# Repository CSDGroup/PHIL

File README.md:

# PHIL

Pipetting Helper Imaging Lid – PHIL - 2021

Latest Update:
15.05.2022 - Updated Arduino Mega Shield to prevent burnouts by increasing the width of motor power traces:
https://www.pcbway.com/project/shareproject/Arduino_Mega14x_V4_3edde2c7.html

Open-source personal pipetting robots with live-​cell incubation and microscopy compatibility

Overview
- personal small desktop liquid handling robot designed in AutoCAD 2018.
- small, light, cheap
- fast self-​assembly from 3D printed and commercial parts
- long-​term live cell culture media exchange, immunostainings, etc
- compatible with microscope stage-​top use during time-​lapse microscopy
- user-​friendly control software

Reference

If you use PHIL please cite the following paper:

Dettinger*, Dettinger*, Kull, Arekatla, Ahmed, Zhang, Schneiter, Wehling, Schirmacher, Kawamura, Loeffler, Schroeder*
Open-source personal pipetting robots with live-cell incubation and microscopy compatibility
Nature Communications 13, 2999 (2022).
https://doi.org/10.1038/s41467-022-30643-7

System Requirements

Hardware requirements

PHILs GUI requires only a standard computer with enough RAM to support the in-memory operations.

Software requirements

OS Requirements

This package is supported for Windows and requires Matlab 2020. The package has been tested on the following systems:

Windows 10 - Matlab 2020

This project is covered under the MIT License.

Download Files
Current version
PHIL_Complete_Resources_210716.zip (ZIP, 47.2 MB)vertical_align_bottom
2021.07.16: Added companies with international shipping options to «Order_List.xlsx» in PHIL_Complete_Resources.zip

Previous versions
2021.07.05: PHIL_Complete_Resources - .zip (ZIP, 47.2 MB)vertical_align_bottom

ZIP file contents
PHIL operation
PHIL_Operation_Instructions.pdf: Complete instructions for using PHIL
PHIL_GUI_210602.m: Executable Matlab script for PHIL gui

PHIL production
Order_List.xlsx: Complete parts list for all required parts
PHIL_Print_Instructions.pdf: Full print settings of all parts
3D print files as described below
PHIL_Assembly_Instructions.pdf: Full instructions for PHIL assembly
PHIL_Arduino_MEGA_14Pump_210216.ino: Complete Arduino sketch for PHIL operation. Requires Accelstepper library installed
 
3D print files
Individual components are encoded by the individual STL files below. You can use these to print them individually.
All required components for a PHIL robot have been grouped into 10 sets for easy simultaneous printing of several components in one print session.

Set_1.stl
Body_VB1.stl: Main body of PHIL
Body_Top_VB1.stl: Frame for mounting Z-axis stepper motors
Elbow_Left_VB1.stl: Left actuator arm for mounting limit switches
Elbow_Right_VB1.stl: Right actuator arm for mounting limit switches
Hands_VB1.stl: Left and right actuator arm
Tube_Plug_VB1.stl: Tube holder for PHIL body

Set_2.stl
Arm_Plate_VB1.stl: Stepper motor mount for left and right arms
Body_Bottom_VB1.stl: Base for main body of PHIL
 
 
Set_3_100infill.stl
LR_Arm_100Infill.stl: Left and right arms for PHIL. To be printed at 100% infill

Set_4.stl
Chamber _VB1.stl: Incubator chamber
2 x Screw_VB1.stl: Screw drives for z-axis
 
 
Set_5.stl
Chamber_Lid_VB1.stl: Lid for incubator chamber
USB_Back_VB1.stl: USB cable mounting bracket, back
USB_Front_VB1.stl: USB cable mounting bracket, front
Handle_VB1.stl: Handle for power control box
Pin_Cup_V1.stl: Pipet holder for normal wells
(Pin_Cup_V1.stl can be replaced with Pin_Cup_Deep_Well_VB1.stl when working with deep well multiwell plates - see instructions)
 
 
Set_6.stl
Power_Box_Left_VB1.stl: Left half of power control box
 
 
Set_7.stl
Power_Box_Right_VB1.stl: Right half of power control box
 
 
Set_8.stl
Arduino_Plate_VB1.stl: Plate for mounting arduinos
 
 
Set_9.stl
Mount_1x_31.stl: 6x mounting brackets for peristaltic pump
 
 
Set_10.stl
Wheel_1x_31.stl: 6x rotors for peristaltic pump

The following files are not required for a PHIL, but help the production:

tube_bender_top_v2.stl: Tube bending press outer body
tube_bender_bot_v2.stl: Tube bending press inner frame
85mm_Tube_cutter_v2.stl: Jig for cutting 85mm segment of peristaltic pump tubing

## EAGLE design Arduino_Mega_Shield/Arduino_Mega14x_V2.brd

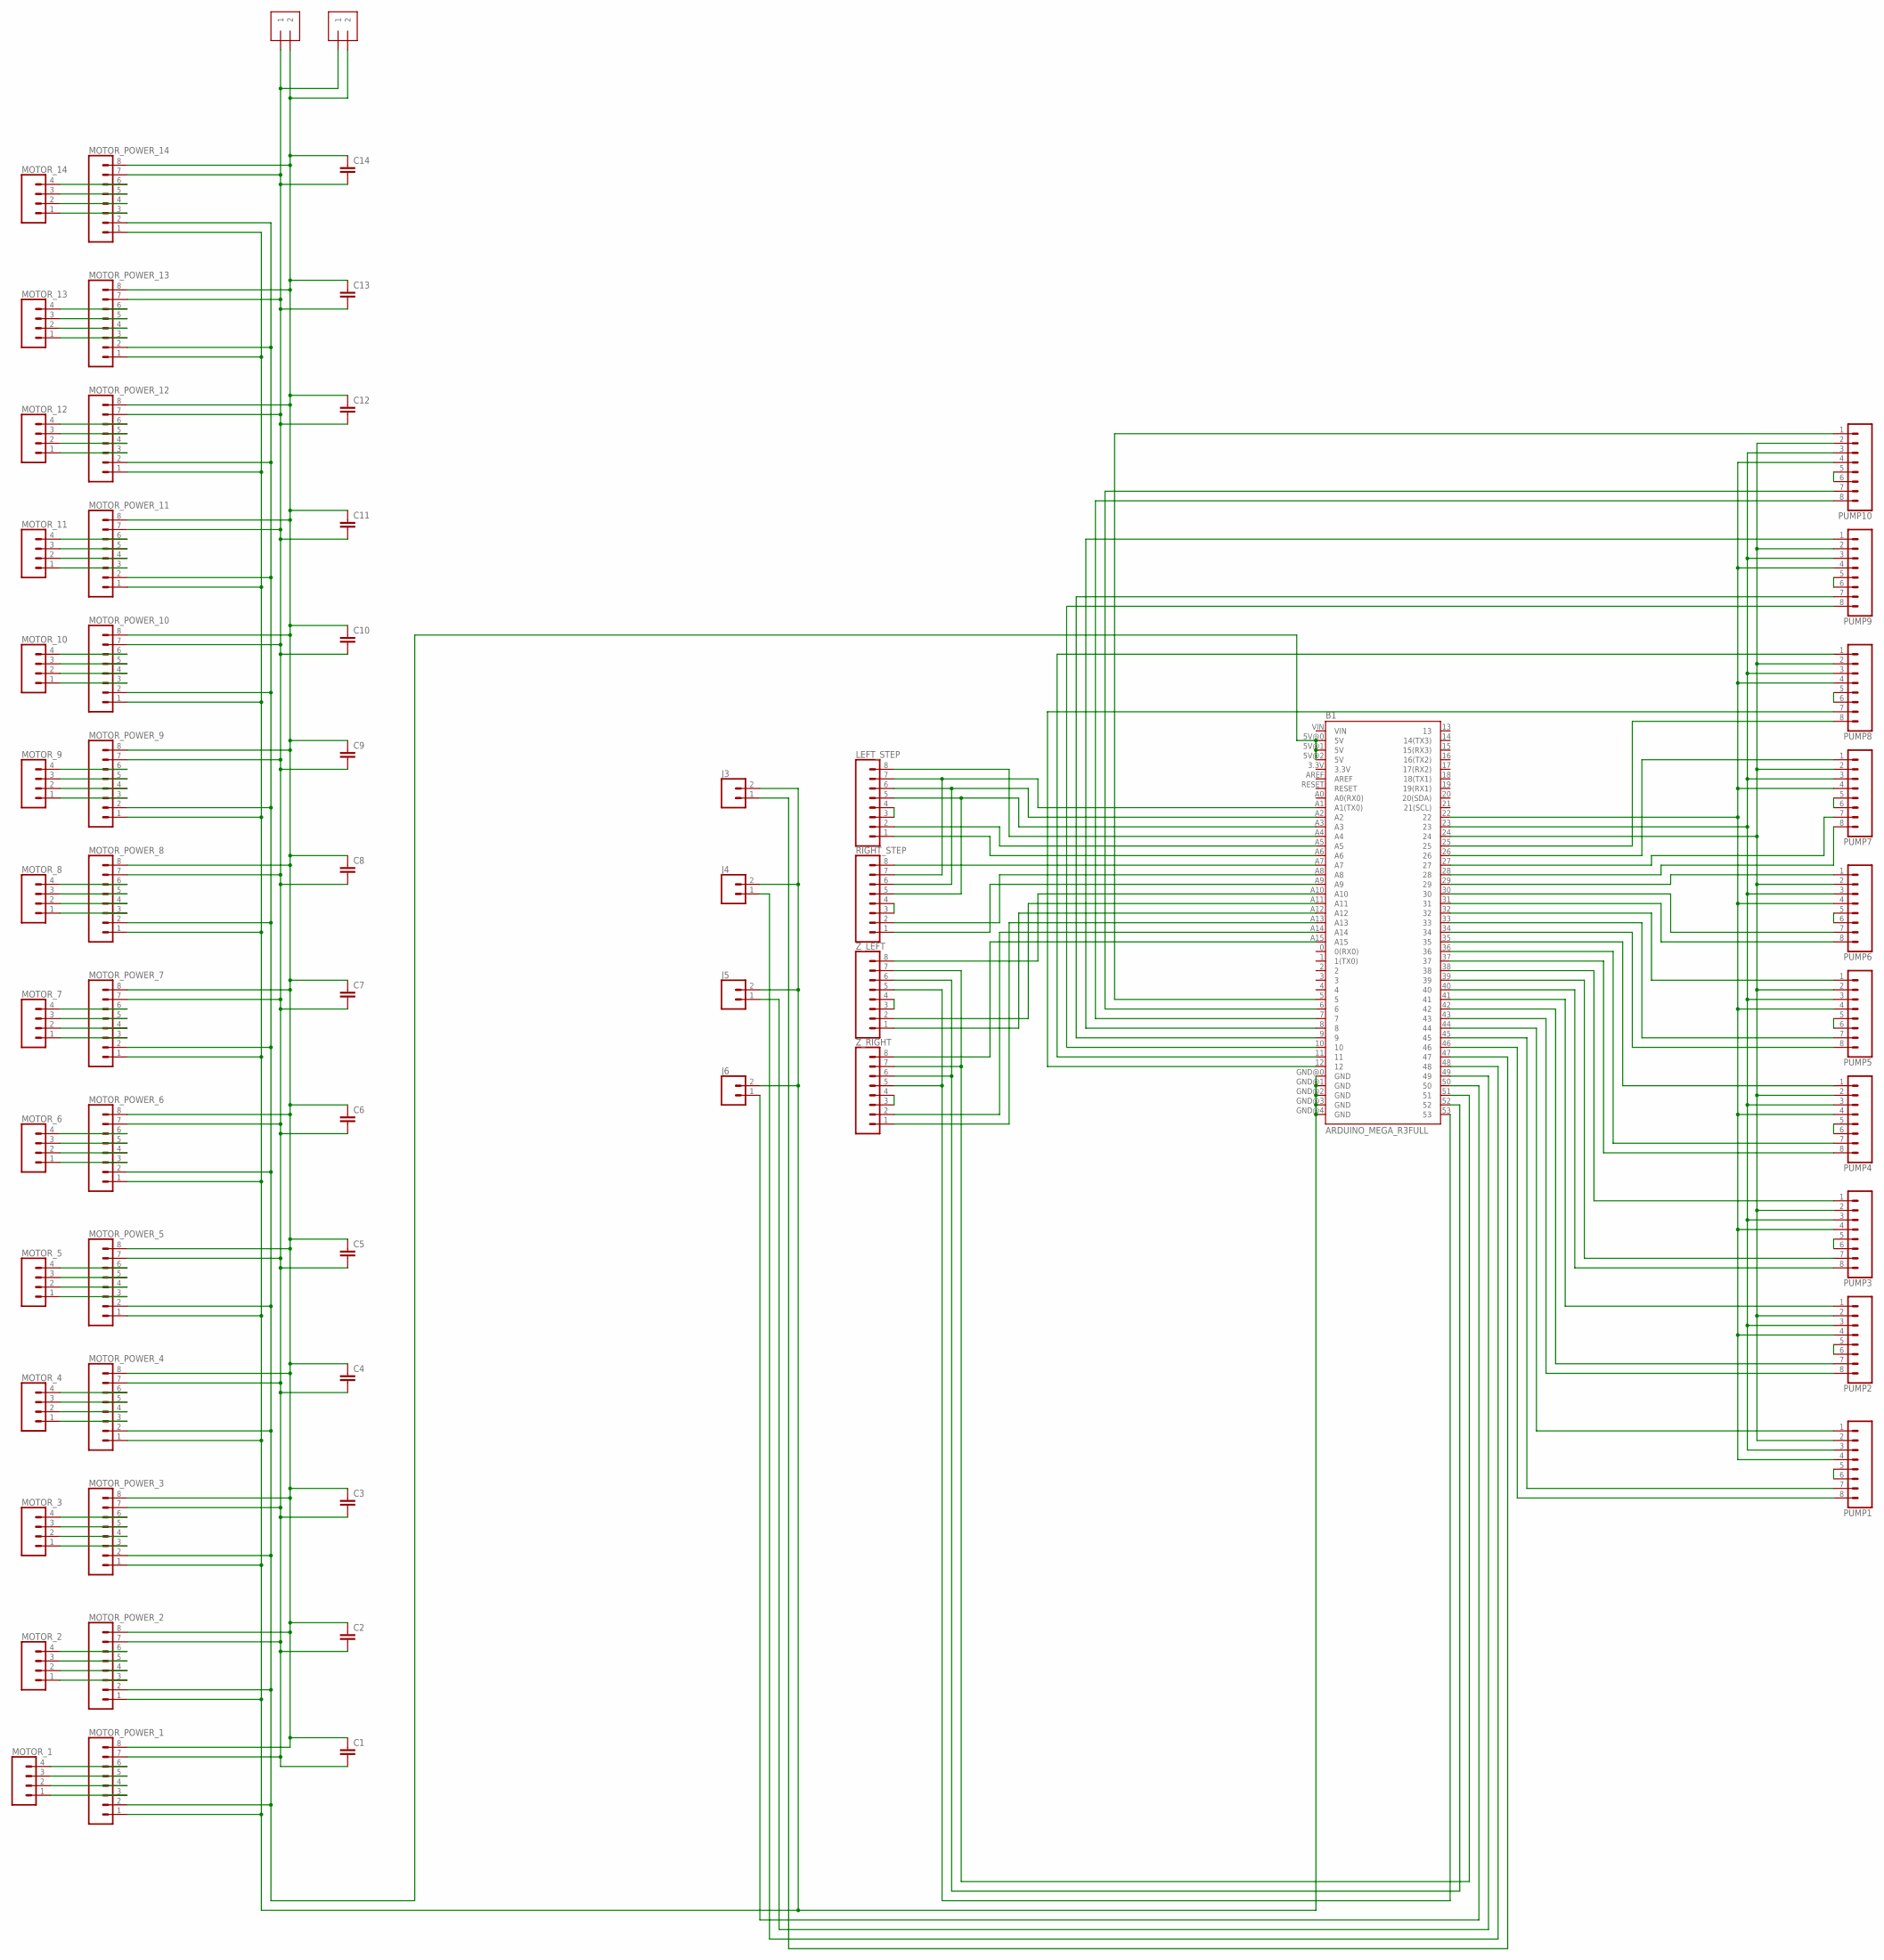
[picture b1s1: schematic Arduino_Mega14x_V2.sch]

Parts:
B1: ARDUINO_MEGA_R3FULL; ARDUINO_MEGA
C1, C2, C3, C4, C5, C6, C7, C8, C9, C10, C11, C12, C13, C14: C5/2.5; C5B2.5
J1, J2: 1X2-3.5MM
J3, J4, J5, J6: CONN_02; 1X02
LEFT_STEP: CONN_08"; 1X08
MOTOR_1, MOTOR_2, MOTOR_3, MOTOR_4, MOTOR_5, MOTOR_6, MOTOR_7, MOTOR_8, MOTOR_9, MOTOR_10, MOTOR_11, MOTOR_12, MOTOR_13, MOTOR_14: CONN_04; 1X04
MOTOR_POWER_1, MOTOR_POWER_2, MOTOR_POWER_3, MOTOR_POWER_4, MOTOR_POWER_5, MOTOR_POWER_6, MOTOR_POWER_7, MOTOR_POWER_8, MOTOR_POWER_9, MOTOR_POWER_10, MOTOR_POWER_11, MOTOR_POWER_12, MOTOR_POWER_13, MOTOR_POWER_14: CONN_08"; 1X08
PUMP1, PUMP2, PUMP3, PUMP4, PUMP5, PUMP6, PUMP7, PUMP8, PUMP9, PUMP10: CONN_08"; 1X08
RIGHT_STEP: CONN_08"; 1X08
Z_LEFT: CONN_08"; 1X08
Z_RIGHT: CONN_08"; 1X08

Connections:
unnamed: MOTOR_1.1, MOTOR_POWER_1.3
unnamed: MOTOR_1.2, MOTOR_POWER_1.4
unnamed: MOTOR_1.3, MOTOR_POWER_1.5
unnamed: LEFT_STEP.3, LEFT_STEP.4
unnamed: MOTOR_1.4, MOTOR_POWER_1.6
unnamed: MOTOR_2.1, MOTOR_POWER_2.3
unnamed: MOTOR_2.2, MOTOR_POWER_2.4
unnamed: RIGHT_STEP.3, RIGHT_STEP.4
unnamed: MOTOR_2.3, MOTOR_POWER_2.5
unnamed: MOTOR_2.4, MOTOR_POWER_2.6
unnamed: MOTOR_3.1, MOTOR_POWER_3.3
unnamed: MOTOR_3.2, MOTOR_POWER_3.4
unnamed: MOTOR_3.3, MOTOR_POWER_3.5
unnamed: MOTOR_3.4, MOTOR_POWER_3.6
unnamed: MOTOR_4.1, MOTOR_POWER_4.3
unnamed: MOTOR_4.2, MOTOR_POWER_4.4
unnamed: MOTOR_4.3, MOTOR_POWER_4.5
unnamed: Z_LEFT.3, Z_LEFT.4
unnamed: MOTOR_4.4, MOTOR_POWER_4.6
unnamed: MOTOR_5.1, MOTOR_POWER_5.3
unnamed: MOTOR_5.2, MOTOR_POWER_5.4
unnamed: MOTOR_5.3, MOTOR_POWER_5.5
unnamed: MOTOR_5.4, MOTOR_POWER_5.6
unnamed: MOTOR_6.1, MOTOR_POWER_6.3
unnamed: Z_RIGHT.3, Z_RIGHT.4
unnamed: MOTOR_6.2, MOTOR_POWER_6.4
unnamed: PUMP1.5, PUMP1.6
unnamed: MOTOR_6.3, MOTOR_POWER_6.5
unnamed: MOTOR_6.4, MOTOR_POWER_6.6
unnamed: MOTOR_7.1, MOTOR_POWER_7.3
unnamed: MOTOR_7.2, MOTOR_POWER_7.4
unnamed: PUMP2.5, PUMP2.6
unnamed: MOTOR_7.3, MOTOR_POWER_7.5
unnamed: MOTOR_7.4, MOTOR_POWER_7.6
unnamed: PUMP3.5, PUMP3.6
unnamed: MOTOR_8.1, MOTOR_POWER_8.3
unnamed: MOTOR_8.2, MOTOR_POWER_8.4
unnamed: MOTOR_8.3, MOTOR_POWER_8.5
unnamed: MOTOR_8.4, MOTOR_POWER_8.6
unnamed: PUMP4.5, PUMP4.6
unnamed: MOTOR_9.1, MOTOR_POWER_9.3
unnamed: MOTOR_9.2, MOTOR_POWER_9.4
unnamed: MOTOR_9.3, MOTOR_POWER_9.5
unnamed: PUMP5.5, PUMP5.6
unnamed: MOTOR_9.4, MOTOR_POWER_9.6
unnamed: MOTOR_10.1, MOTOR_POWER_10.3
unnamed: MOTOR_10.2, MOTOR_POWER_10.4
unnamed: PUMP6.5, PUMP6.6
unnamed: MOTOR_10.3, MOTOR_POWER_10.5
unnamed: MOTOR_10.4, MOTOR_POWER_10.6
unnamed: MOTOR_11.1, MOTOR_POWER_11.3
unnamed: PUMP7.5, PUMP7.6
unnamed: MOTOR_11.2, MOTOR_POWER_11.4
unnamed: MOTOR_11.3, MOTOR_POWER_11.5
unnamed: MOTOR_11.4, MOTOR_POWER_11.6
unnamed: PUMP8.5, PUMP8.6
unnamed: MOTOR_12.1, MOTOR_POWER_12.3
unnamed: MOTOR_12.2, MOTOR_POWER_12.4
unnamed: MOTOR_12.3, MOTOR_POWER_12.5
unnamed: PUMP9.5, PUMP9.6
unnamed: MOTOR_12.4, MOTOR_POWER_12.6
unnamed: MOTOR_13.1, MOTOR_POWER_13.3
unnamed: MOTOR_13.2, MOTOR_POWER_13.4
unnamed: PUMP10.5, PUMP10.6
unnamed: MOTOR_13.3, MOTOR_POWER_13.5
unnamed: MOTOR_13.4, MOTOR_POWER_13.6
unnamed: MOTOR_14.1, MOTOR_POWER_14.3
unnamed: MOTOR_14.2, MOTOR_POWER_14.4
unnamed: MOTOR_14.3, MOTOR_POWER_14.5
unnamed: MOTOR_14.4, MOTOR_POWER_14.6
unnamed: B1.GND@0 (GND), B1.GND@1 (GND), B1.GND@2 (GND), B1.GND@3 (GND), B1.GND@4 (GND), J3.2, J4.2, J5.2, J6.2, MOTOR_POWER_1.1, MOTOR_POWER_2.1, MOTOR_POWER_3.1, MOTOR_POWER_4.1, MOTOR_POWER_5.1, MOTOR_POWER_6.1, MOTOR_POWER_7.1, MOTOR_POWER_8.1, MOTOR_POWER_9.1, MOTOR_POWER_10.1, MOTOR_POWER_11.1, MOTOR_POWER_12.1, MOTOR_POWER_13.1, MOTOR_POWER_14.1
unnamed: B1.A1 (A1(TX0)), LEFT_STEP.7, RIGHT_STEP.7
unnamed: B1.A2, LEFT_STEP.6, RIGHT_STEP.6
unnamed: B1.A3, LEFT_STEP.5, RIGHT_STEP.5
unnamed: B1.51, Z_LEFT.7, Z_RIGHT.7
unnamed: B1.52, Z_LEFT.6, Z_RIGHT.6
unnamed: B1.53, Z_LEFT.5, Z_RIGHT.5
unnamed: B1.22, PUMP1.4, PUMP2.4, PUMP3.4, PUMP4.4, PUMP5.4, PUMP6.4, PUMP7.4, PUMP8.4, PUMP9.4, PUMP10.4
unnamed: B1.23, PUMP1.3, PUMP2.3, PUMP3.3, PUMP4.3, PUMP5.3, PUMP6.3, PUMP7.3, PUMP8.3, PUMP9.3, PUMP10.3
unnamed: B1.24, PUMP1.2, PUMP2.2, PUMP3.2, PUMP4.2, PUMP5.2, PUMP6.2, PUMP7.2, PUMP8.2, PUMP9.2, PUMP10.2
unnamed: B1.A15, Z_RIGHT.8
unnamed: B1.5V@0 (5V), B1.5V@1 (5V), B1.5V@2 (5V), MOTOR_POWER_1.2, MOTOR_POWER_2.2, MOTOR_POWER_3.2, MOTOR_POWER_4.2, MOTOR_POWER_5.2, MOTOR_POWER_6.2, MOTOR_POWER_7.2, MOTOR_POWER_8.2, MOTOR_POWER_9.2, MOTOR_POWER_10.2, MOTOR_POWER_11.2, MOTOR_POWER_12.2, MOTOR_POWER_13.2, MOTOR_POWER_14.2
unnamed: C1.2, C2.2, C3.2, C4.2, C5.2, C6.2, C7.2, C8.2, C9.2, C10.2, C11.2, C12.2, C13.2, C14.2, J1.1, J2.1, MOTOR_POWER_1.7, MOTOR_POWER_2.7, MOTOR_POWER_3.7, MOTOR_POWER_4.7, MOTOR_POWER_5.7, MOTOR_POWER_6.7, MOTOR_POWER_7.7, MOTOR_POWER_8.7, MOTOR_POWER_9.7, MOTOR_POWER_10.7, MOTOR_POWER_11.7, MOTOR_POWER_12.7, MOTOR_POWER_13.7, MOTOR_POWER_14.7
unnamed: C1.1, C2.1, C3.1, C4.1, C5.1, C6.1, C7.1, C8.1, C9.1, C10.1, C11.1, C12.1, C13.1, C14.1, J1.2, J2.2, MOTOR_POWER_1.8, MOTOR_POWER_2.8, MOTOR_POWER_3.8, MOTOR_POWER_4.8, MOTOR_POWER_5.8, MOTOR_POWER_6.8, MOTOR_POWER_7.8, MOTOR_POWER_8.8, MOTOR_POWER_9.8, MOTOR_POWER_10.8, MOTOR_POWER_11.8, MOTOR_POWER_12.8, MOTOR_POWER_13.8, MOTOR_POWER_14.8
unnamed: B1.A14, Z_RIGHT.2
unnamed: B1.A13, Z_RIGHT.1
unnamed: B1.A12, Z_LEFT.1
unnamed: B1.A11, Z_LEFT.2
unnamed: B1.A10, Z_LEFT.8
unnamed: B1.A9, RIGHT_STEP.1
unnamed: B1.A8, RIGHT_STEP.2
unnamed: B1.A7, RIGHT_STEP.8
unnamed: B1.A6, LEFT_STEP.1
unnamed: B1.A5, LEFT_STEP.2
unnamed: B1.A4, LEFT_STEP.8
unnamed: B1.50, J6.1
unnamed: B1.49, J5.1
unnamed: B1.48, J4.1
unnamed: B1.47, J3.1
unnamed: B1.46, PUMP1.8
unnamed: B1.45, PUMP1.7
unnamed: B1.44, PUMP1.1
unnamed: B1.43, PUMP2.8
unnamed: B1.42, PUMP2.7
unnamed: B1.41, PUMP2.1
unnamed: B1.40, PUMP3.8
unnamed: B1.39, PUMP3.7
unnamed: B1.38, PUMP3.1
unnamed: B1.37, PUMP4.8
unnamed: B1.36, PUMP4.7
unnamed: B1.35, PUMP4.1
unnamed: B1.34, PUMP5.8
unnamed: B1.33, PUMP5.7
unnamed: B1.32, PUMP5.1
unnamed: B1.31, PUMP6.8
unnamed: B1.30, PUMP6.7
unnamed: B1.29, PUMP6.1
unnamed: B1.28, PUMP7.8
unnamed: B1.27, PUMP7.7
unnamed: B1.26, PUMP7.1
unnamed: B1.25, PUMP8.8
unnamed: B1.12, PUMP8.7
unnamed: B1.11, PUMP8.1
unnamed: B1.10, PUMP9.8
unnamed: B1.9, PUMP9.7
unnamed: B1.8, PUMP9.1
unnamed: B1.7, PUMP10.8
unnamed: B1.6, PUMP10.7
unnamed: B1.5, PUMP10.1

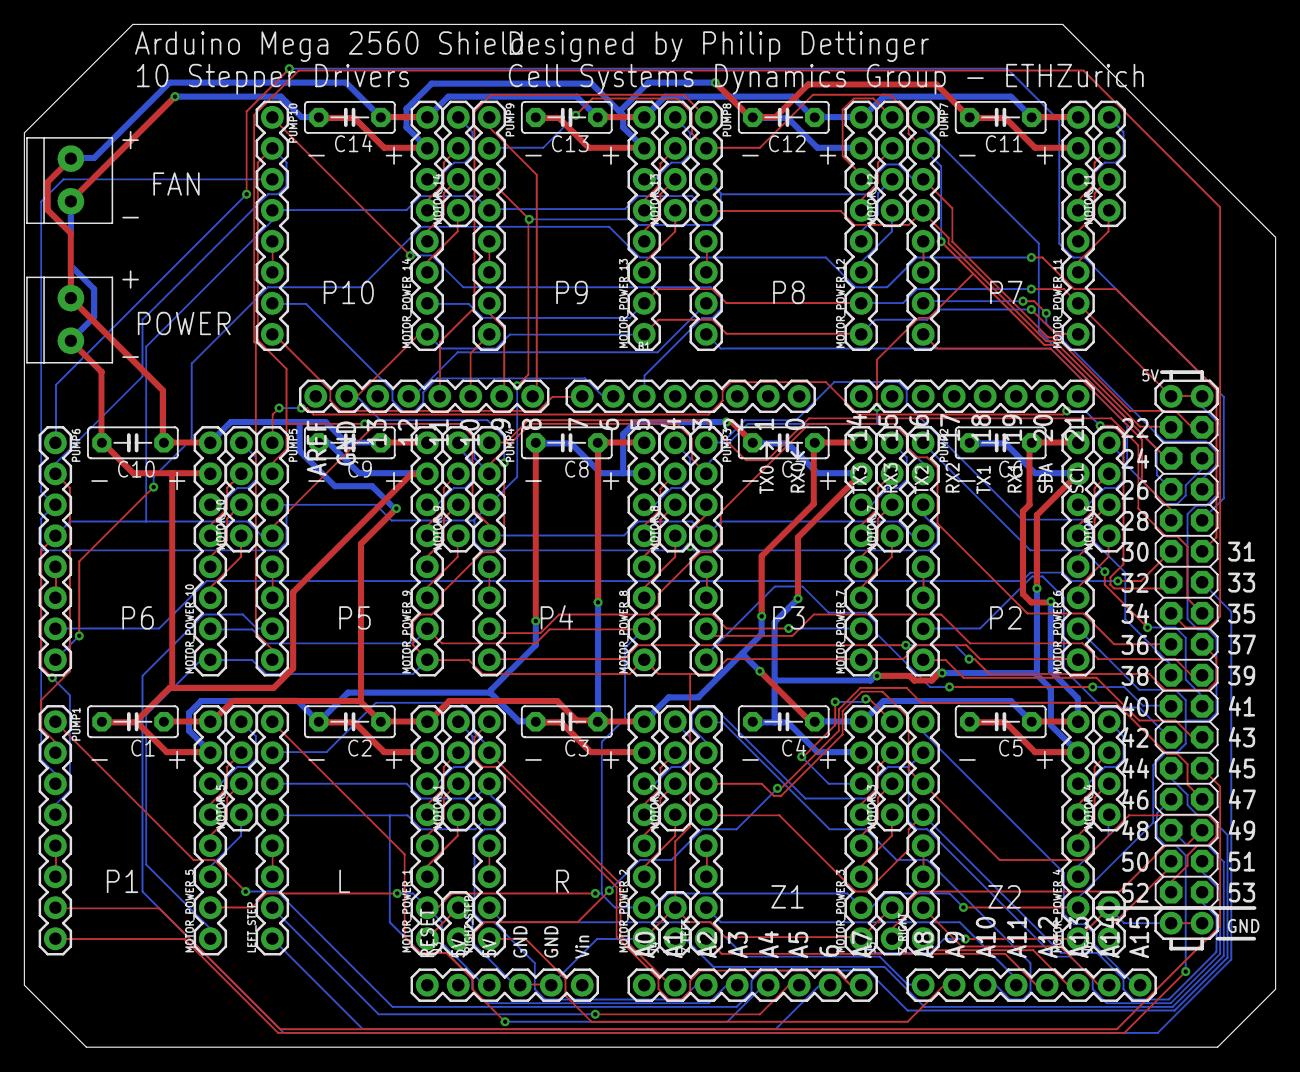
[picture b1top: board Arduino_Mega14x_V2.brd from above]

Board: 2 copper layers, 102.5 x 83.8 mm, 63 parts (0 on the bottom side), 129 nets.

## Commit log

2022-05-15 Add files via upload
    Updated Arduino shield
2022-05-20 Add files via upload
    Updated Arduino sketch which fixes a bug in the command string processing loop.
2022-05-20 Add files via upload
    Updated GUI including a configuration file.
2025-10-28 Update Reference to Nat Comm.

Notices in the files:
parts and their libraries:
SparkFun-Connectors: Licensing: Creative Commons ShareAlike 4.0 International - https://creativecommons.org/licenses/by-sa/4.0
